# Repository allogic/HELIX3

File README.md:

# HELIX3
Dual 3-Phase BLDC-Motor Driver Board

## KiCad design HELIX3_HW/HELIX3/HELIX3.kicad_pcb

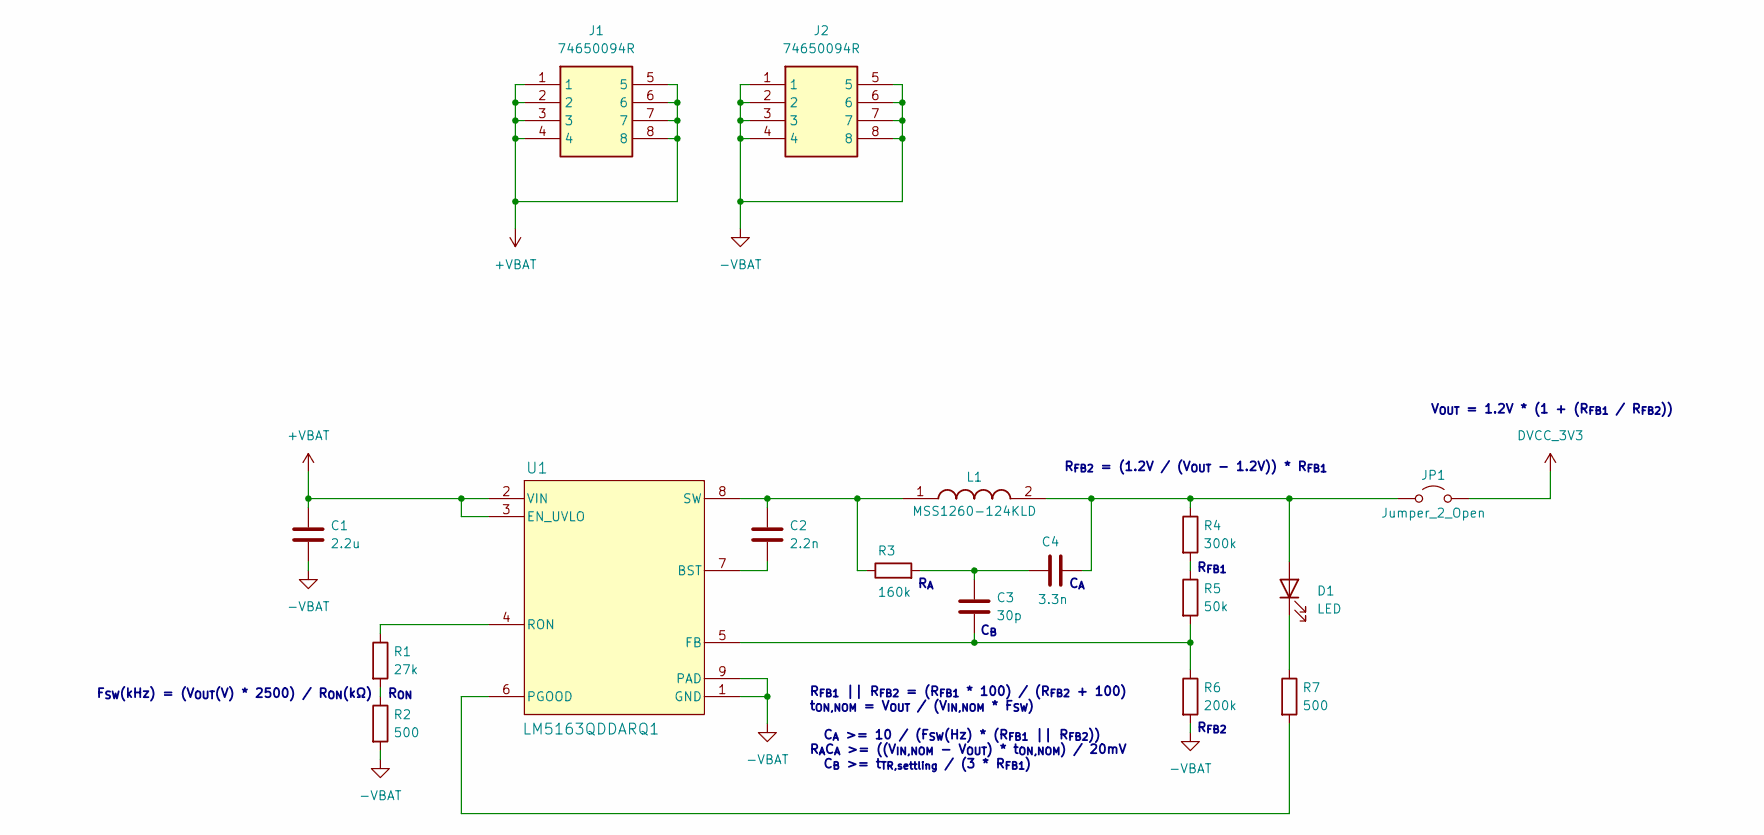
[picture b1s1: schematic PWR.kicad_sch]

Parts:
C1: 2.2u; C_1210_3225Metric
C2: 2.2n; C_0603_1608Metric
C3: 30p; C_0603_1608Metric
C4: 3.3n; C_0603_1608Metric
D1: LED; LED_0603_1608Metric
J1, J2: 74650094R; Manufacturer_Part_Number 74650094R; Mouser Part Number 710-74650094R
JP1: Jumper_2_Open; SolderJumper-2_P1.3mm_Open_Pad1.0x1.5mm
L1: MSS1260-124KLD; Manufacturer_Part_Number MSS1260-124KLD; Mouser Part Number 994-MSS1260-124KLD
R1: 27k; R_0603_1608Metric
R2, R7: 500; R_0603_1608Metric
R3: 160k; R_0603_1608Metric
R4: 300k; R_0603_1608Metric
R5: 50k; R_0603_1608Metric
R6: 200k; R_0603_1608Metric
U1: LM5163QDDARQ1

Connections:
+VBAT: C1.1, J1.1, J1.2, J1.3, J1.4, J1.5, J1.6, J1.7, J1.8, U1.2 (VIN), U1.3 (EN_UVLO); also elsewhere on the board
-VBAT: C1.2, J2.1, J2.2, J2.3, J2.4, J2.5, J2.6, J2.7, J2.8, R2.2, R6.2, U1.1 (GND), U1.9 (PAD); also elsewhere on the board
DVCC_3V3: JP1.2 (B); also elsewhere on the board
unnamed: C3.1, C4.1, R3.2
unnamed: C4.2, D1.2 (A), JP1.1 (A), L1.2, R4.1
unnamed: D1.1 (K), R7.1
unnamed: R1.2, R2.1
unnamed: R4.2, R5.1
unnamed: C2.2, U1.7 (BST)
unnamed: C3.2, R5.2, R6.1, U1.5 (FB)
unnamed: R7.2, U1.6 (PGOOD)
unnamed: R1.1, U1.4 (RON)
unnamed: C2.1, L1.1, R3.1, U1.8 (SW)

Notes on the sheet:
R_{ON}
C_{B}
R_{FB1}
R_{A}
R_{FB2} = (1.2V / (V_{OUT} - 1.2V)) * R_{FB1}
C_{A}
R_{FB1} || R_{FB2} = (R_{FB1} * 100) / (R_{FB2} + 100) t_{ON,NOM} = V_{OUT} / (V_{IN,NOM} * F_{SW}) C_{A} >= 10 / (F_{SW}(Hz) * (R_{FB1} || R_{FB2})) R_{A}C_{A} >= ((V_{IN,NOM} - V_{OUT}) * t_{ON,NOM}) / 20mV C_{B} >= t_{TR,settling} / (3 * R_{FB1})
F_{SW}(kHz) = (V_{OUT}(V) * 2500) / R_{ON}(kΩ)
V_{OUT} = 1.2V * (1 + (R_{FB1} / R_{FB2}))
R_{FB2}

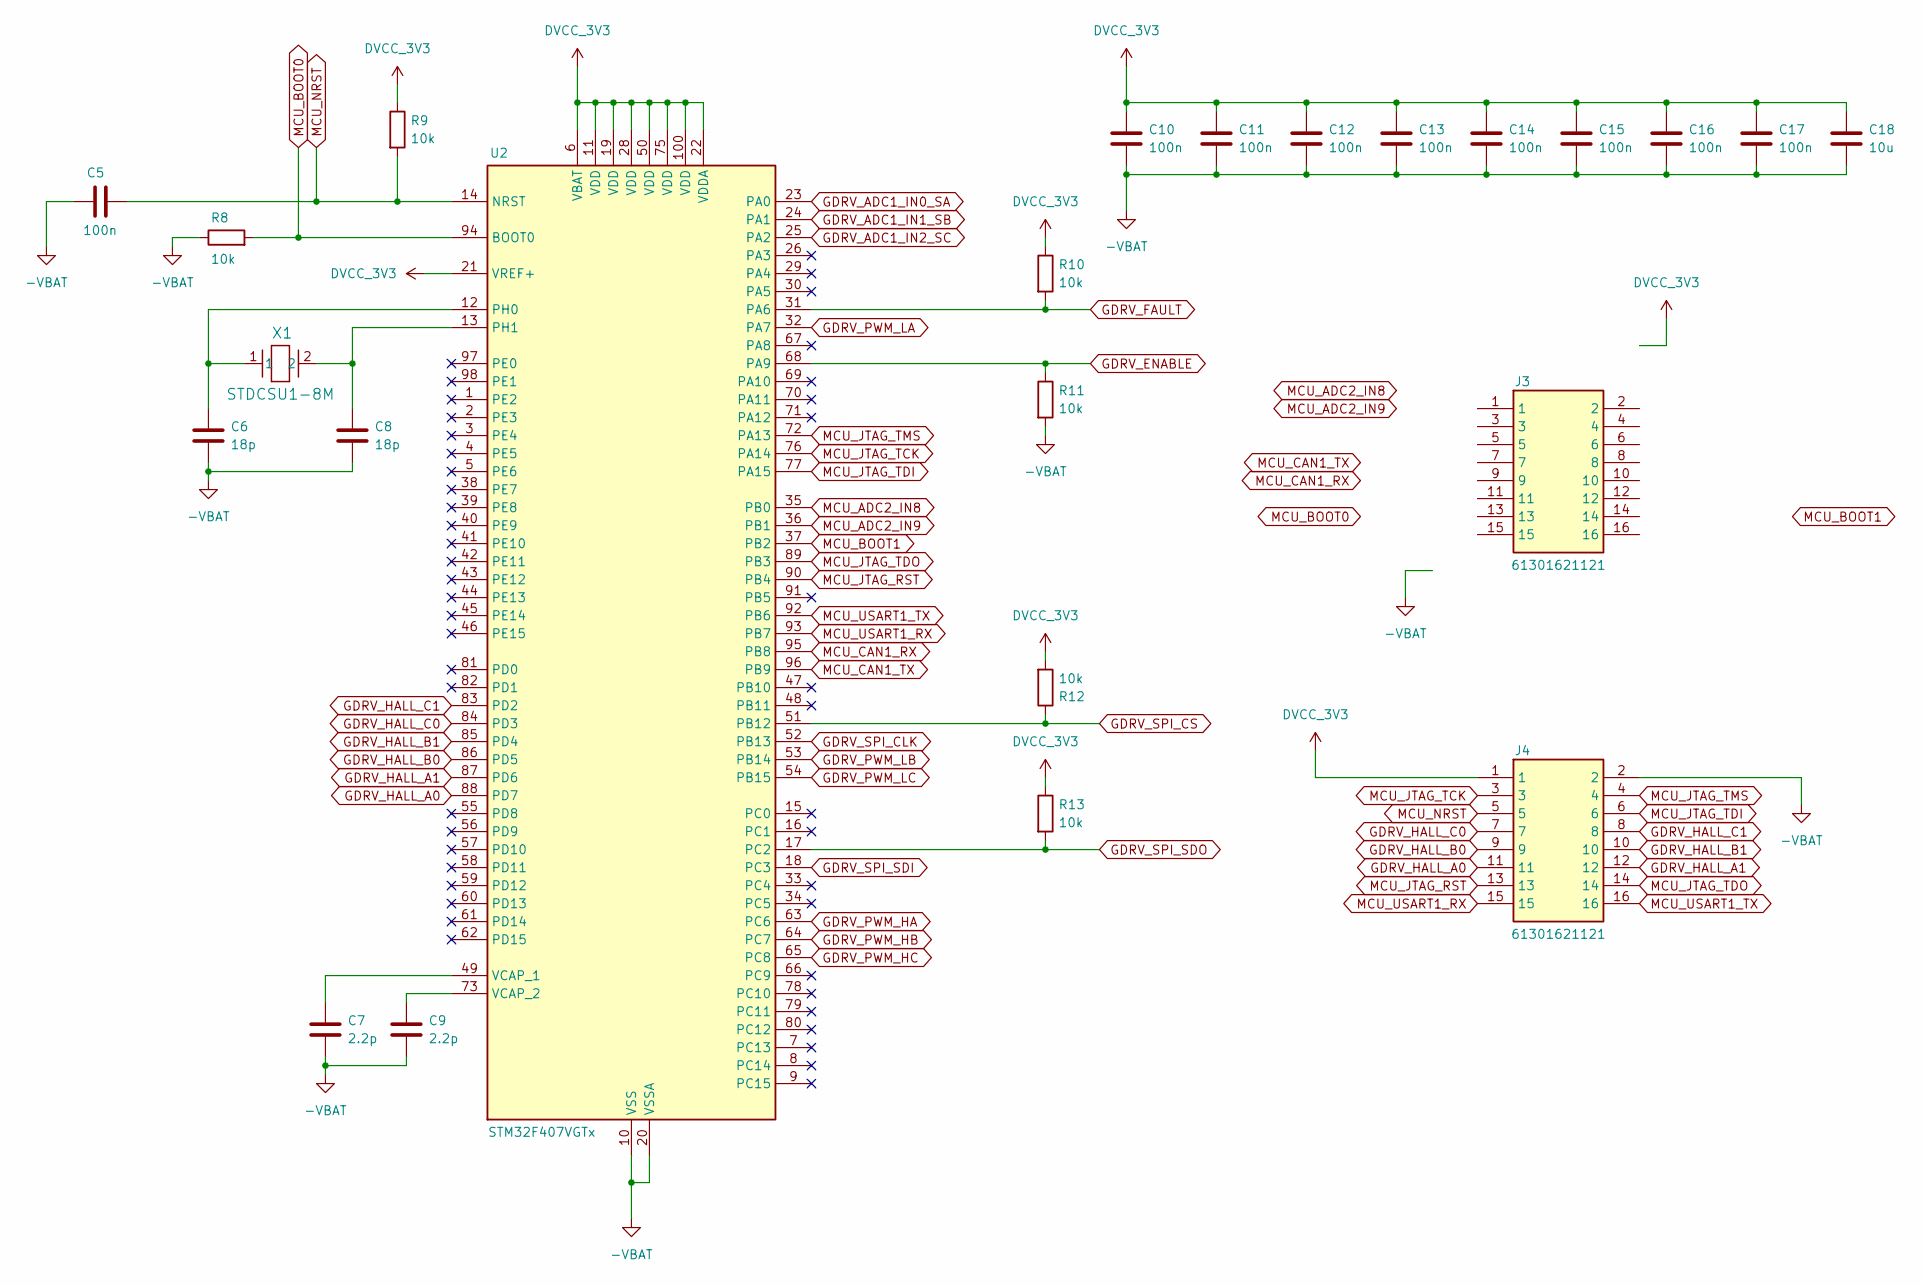
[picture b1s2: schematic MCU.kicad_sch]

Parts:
C5, C10, C11, C12, C13, C14, C15, C16, C17: 100n; C_0603_1608Metric
C6, C8: 18p; C_0603_1608Metric
C7, C9: 2.2p; C_0603_1608Metric
C18: 10u; C_2220_5750Metric
J3, J4: 61301621121; Manufacturer_Part_Number 61301621121; Mouser Part Number 710-61301621121
R8, R9, R10, R11, R12, R13: 10k; R_0603_1608Metric
U2: STM32F407VGTx; LQFP-100_14x14mm_P0.5mm
X1: STDCSU1-8M

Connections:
-VBAT: C5.1, C6.2, C7.2, C8.2, C9.2, C10.2, C11.2, C12.2, C13.2, C14.2, C15.2, C16.2, C17.2, C18.2, J4.2, R8.1, R11.2, U2.10 (VSS), U2.20 (VSSA), U2.27 (VSS), U2.74 (VSS), U2.99 (VSS); also elsewhere on the board
DVCC_3V3: C10.1, C11.1, C12.1, C13.1, C14.1, C15.1, C16.1, C17.1, C18.1, J4.1, R9.1, R10.1, R12.2, R13.1, U2.6 (VBAT), U2.11 (VDD), U2.19 (VDD), U2.21 (VREF+), U2.22 (VDDA), U2.28 (VDD), U2.50 (VDD), U2.75 (VDD), U2.100 (VDD); also elsewhere on the board
GDRV_ADC1_IN0_SA: U2.23 (PA0); also elsewhere on the board
GDRV_ADC1_IN1_SB: U2.24 (PA1); also elsewhere on the board
GDRV_ADC1_IN2_SC: U2.25 (PA2); also elsewhere on the board
GDRV_ENABLE: R11.1, U2.68 (PA9); also elsewhere on the board
GDRV_FAULT: R10.2, U2.31 (PA6); also elsewhere on the board
GDRV_HALL_A0: J4.11, U2.88 (PD7)
GDRV_HALL_A1: J4.12, U2.87 (PD6)
GDRV_HALL_B0: J4.9, U2.86 (PD5)
GDRV_HALL_B1: J4.10, U2.85 (PD4)
GDRV_HALL_C0: J4.7, U2.84 (PD3)
GDRV_HALL_C1: J4.8, U2.83 (PD2)
GDRV_PWM_HA: U2.63 (PC6); also elsewhere on the board
GDRV_PWM_HB: U2.64 (PC7); also elsewhere on the board
GDRV_PWM_HC: U2.65 (PC8); also elsewhere on the board
GDRV_PWM_LA: U2.32 (PA7); also elsewhere on the board
GDRV_PWM_LB: U2.53 (PB14); also elsewhere on the board
GDRV_PWM_LC: U2.54 (PB15); also elsewhere on the board
GDRV_SPI_CLK: U2.52 (PB13); also elsewhere on the board
GDRV_SPI_CS: R12.1, U2.51 (PB12); also elsewhere on the board
GDRV_SPI_SDI: U2.18 (PC3); also elsewhere on the board
GDRV_SPI_SDO: R13.2, U2.17 (PC2); also elsewhere on the board
MCU_ADC2_IN8: U2.35 (PB0)
MCU_ADC2_IN9: U2.36 (PB1)
MCU_BOOT0: R8.2, U2.94 (BOOT0)
MCU_BOOT1: U2.37 (PB2)
MCU_CAN1_RX: U2.95 (PB8)
MCU_CAN1_TX: U2.96 (PB9)
MCU_JTAG_RST: J4.13, U2.90 (PB4)
MCU_JTAG_TCK: J4.3, U2.76 (PA14)
MCU_JTAG_TDI: J4.6, U2.77 (PA15)
MCU_JTAG_TDO: J4.14, U2.89 (PB3)
MCU_JTAG_TMS: J4.4, U2.72 (PA13)
MCU_NRST: C5.2, J4.5, R9.2, U2.14 (NRST)
MCU_USART1_RX: J4.15, U2.93 (PB7)
MCU_USART1_TX: J4.16, U2.92 (PB6)
unnamed: C6.1, U2.12 (PH0), X1.1
unnamed: C8.1, U2.13 (PH1), X1.2
unnamed: C7.1, U2.49 (VCAP_1)
unnamed: C9.1, U2.73 (VCAP_2)

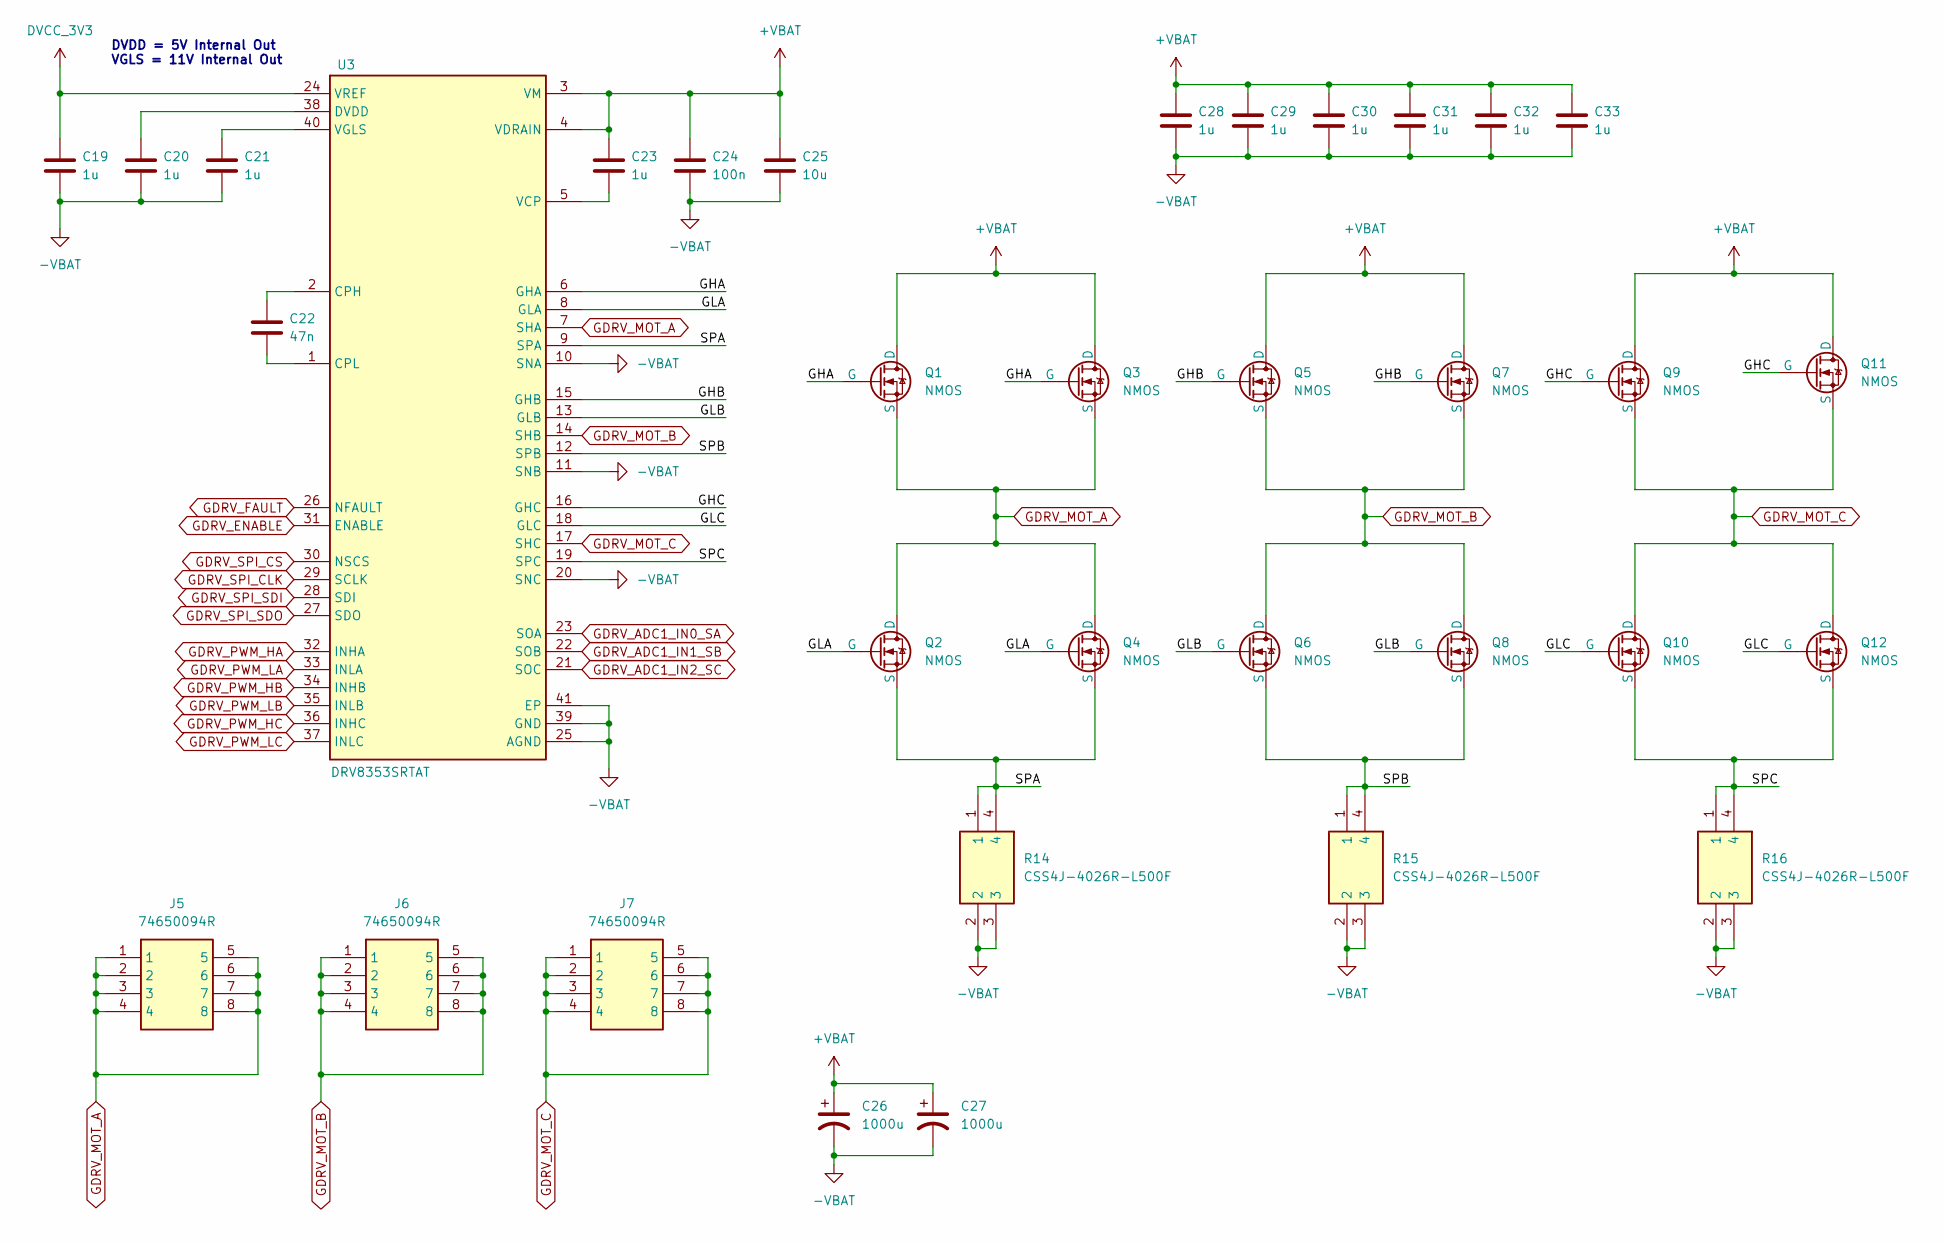
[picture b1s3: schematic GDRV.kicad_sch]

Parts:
C19, C20, C21: 1u; C_0603_1608Metric
C22: 47n; C_0603_1608Metric
C23, C28, C29, C30, C31, C32, C33: 1u; C_0805_2012Metric
C24: 100n; C_0603_1608Metric
C25: 10u; C_2220_5750Metric
C26, C27: 1000u; EKYB101ELL102MM40S
J5, J6, J7: 74650094R; Manufacturer_Part_Number 74650094R; Mouser Part Number 710-74650094R
Q1, Q2, Q3, Q4, Q5, Q6, Q7, Q8, Q9, Q10, Q11, Q12: NMOS; CSD19536KCS
R14, R15, R16: CSS4J-4026R-L500F; Manufacturer_Part_Number CSS4J-4026R-L500F; Mouser Part Number 652-CSS4J4026RL500F
U3: DRV8353SRTAT; Manufacturer_Part_Number DRV8353SRTAT; Mouser Part Number 595-DRV8353SRTAT

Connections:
+VBAT: C23.1, C24.1, C25.1, C26.1, C27.1, C28.1, C29.1, C30.1, C31.1, C32.1, C33.1, Q1.1 (D), Q3.1 (D), Q5.1 (D), Q7.1 (D), Q9.1 (D), Q11.1 (D), U3.3 (VM), U3.4 (VDRAIN); also elsewhere on the board
-VBAT: C19.2, C20.2, C21.2, C24.2, C25.2, C26.2, C27.2, C28.2, C29.2, C30.2, C31.2, C32.2, C33.2, R14.2, R14.3, R15.2, R15.3, R16.2, R16.3, U3.10 (SNA), U3.11 (SNB), U3.20 (SNC), U3.25 (AGND), U3.39 (GND), U3.41 (EP); also elsewhere on the board
/GDRV/GHA: Q1.2 (G), Q3.2 (G), U3.6 (GHA)
/GDRV/GHB: Q5.2 (G), Q7.2 (G), U3.15 (GHB)
/GDRV/GHC: Q9.2 (G), Q11.2 (G), U3.16 (GHC)
/GDRV/GLA: Q2.2 (G), Q4.2 (G), U3.8 (GLA)
/GDRV/GLB: Q6.2 (G), Q8.2 (G), U3.13 (GLB)
/GDRV/GLC: Q10.2 (G), Q12.2 (G), U3.18 (GLC)
/GDRV/SPA: Q2.3 (S), Q4.3 (S), R14.1, R14.4, U3.9 (SPA)
/GDRV/SPB: Q6.3 (S), Q8.3 (S), R15.1, R15.4, U3.12 (SPB)
/GDRV/SPC: Q10.3 (S), Q12.3 (S), R16.1, R16.4, U3.19 (SPC)
DVCC_3V3: C19.1, U3.24 (VREF); also elsewhere on the board
GDRV_ADC1_IN0_SA: U3.23 (SOA); also elsewhere on the board
GDRV_ADC1_IN1_SB: U3.22 (SOB); also elsewhere on the board
GDRV_ADC1_IN2_SC: U3.21 (SOC); also elsewhere on the board
GDRV_ENABLE: U3.31 (ENABLE); also elsewhere on the board
GDRV_FAULT: U3.26 (NFAULT); also elsewhere on the board
GDRV_MOT_A: J5.1, J5.2, J5.3, J5.4, J5.5, J5.6, J5.7, J5.8, Q1.3 (S), Q2.1 (D), Q3.3 (S), Q4.1 (D), U3.7 (SHA)
GDRV_MOT_B: J6.1, J6.2, J6.3, J6.4, J6.5, J6.6, J6.7, J6.8, Q5.3 (S), Q6.1 (D), Q7.3 (S), Q8.1 (D), U3.14 (SHB)
GDRV_MOT_C: J7.1, J7.2, J7.3, J7.4, J7.5, J7.6, J7.7, J7.8, Q9.3 (S), Q10.1 (D), Q11.3 (S), Q12.1 (D), U3.17 (SHC)
GDRV_PWM_HA: U3.32 (INHA); also elsewhere on the board
GDRV_PWM_HB: U3.34 (INHB); also elsewhere on the board
GDRV_PWM_HC: U3.36 (INHC); also elsewhere on the board
GDRV_PWM_LA: U3.33 (INLA); also elsewhere on the board
GDRV_PWM_LB: U3.35 (INLB); also elsewhere on the board
GDRV_PWM_LC: U3.37 (INLC); also elsewhere on the board
GDRV_SPI_CLK: U3.29 (SCLK); also elsewhere on the board
GDRV_SPI_CS: U3.30 (NSCS); also elsewhere on the board
GDRV_SPI_SDI: U3.28 (SDI); also elsewhere on the board
GDRV_SPI_SDO: U3.27 (SDO); also elsewhere on the board
unnamed: C22.1, U3.2 (CPH)
unnamed: C22.2, U3.1 (CPL)
unnamed: C20.1, U3.38 (DVDD)
unnamed: C23.2, U3.5 (VCP)
unnamed: C21.1, U3.40 (VGLS)

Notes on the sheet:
DVDD = 5V Internal Out VGLS = 11V Internal Out

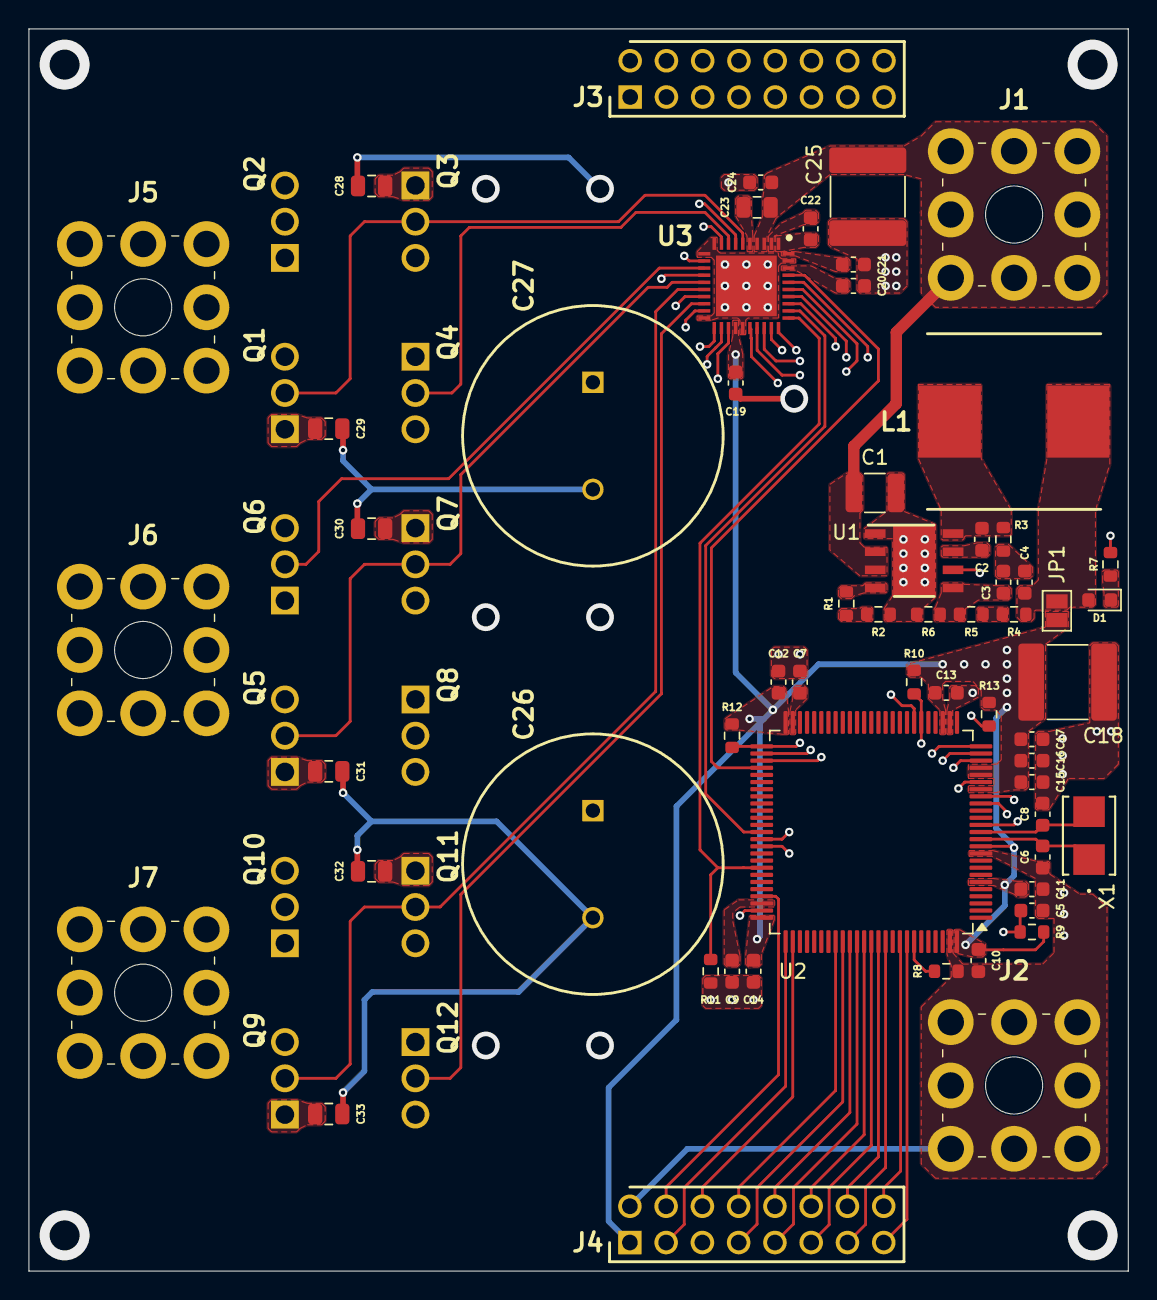
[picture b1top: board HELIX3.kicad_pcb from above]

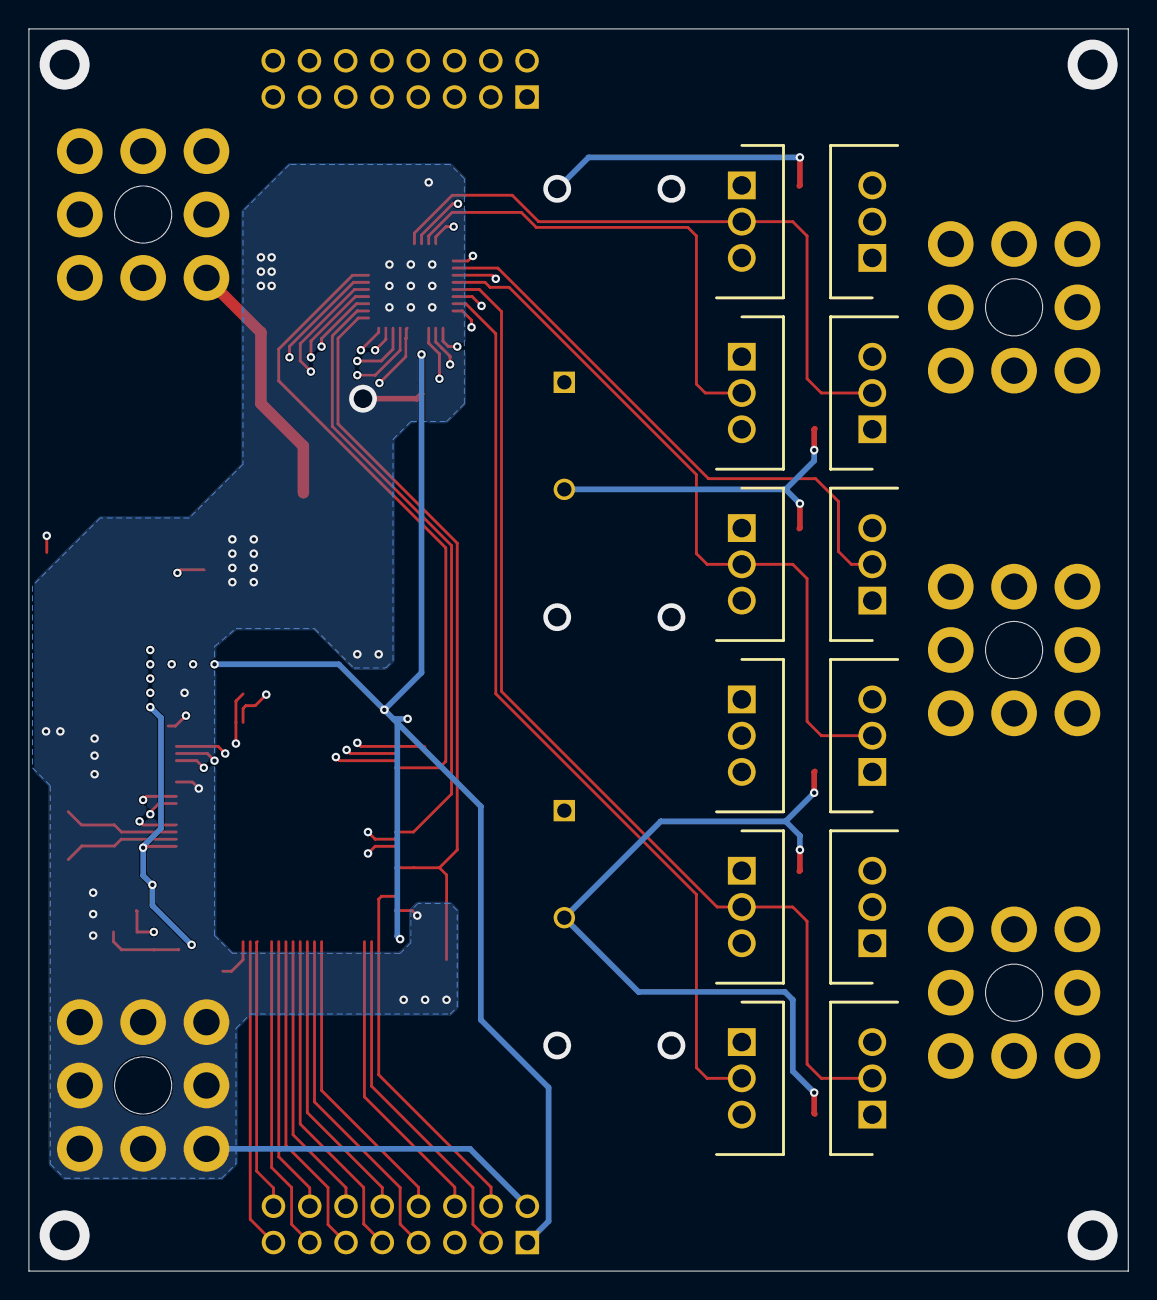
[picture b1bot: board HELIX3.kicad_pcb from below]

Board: 4 copper layers, 77.0 x 87.0 mm, 72 parts (12 on the bottom side), 64 nets.
